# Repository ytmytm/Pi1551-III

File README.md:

# Pi1551-III

A **1551 floppy emulator** for Commodore C16, C116 and Plus/4, in the same mechanical and aesthetic package as the [C64 Pi1541-III](https://github.com/tebl/C64-Pi1541-III): Raspberry Pi 3–based, 1.3" OLED, rotary encoder, and stack of PCBs with faceplates. 

This variant uses the **[Pi1551](https://github.com/ytmytm/Pi1551)** firmware and connects to the computer via **[tcbm2sd](https://github.com/ytmytm/plus4-tcbm2sd)** (TCBM bus). It also adds a **MiniDIN-7** port for **TAP tape playback** with a simple 1:1 male-to-male cable to the machine’s tape port.

> **WARNING — tcbm2sd only**  
> This device must **only** be connected to a **tcbm2sd** adapter. **Do not** connect it to an original 1551 paddle or any other 5 V bus. The interface is **not 5 V tolerant** and can damage the Raspberry Pi and the computer.

---

**Build files:** Gerbers for every board, plus BOM and SMD position files for the main module (Pi1551-III Module-rotated), are published in the **[Releases](https://github.com/ytmytm/Pi1551-III/releases)** section of this repository.

If you prefer a smaller, simpler board: see **[Pi1551-HAT](https://github.com/ytmytm/Pi1551-HAT)** for a minimal Raspberry Pi HAT with the same 1551 + TAP functionality with several features optional.

---

- [1. Modules](#1-modules)
- [2. Differences from Pi1541-III](#2-differences-from-pi1541-iii)
- [3. Assembly](#3-assembly)
- [4. Cables](#4-cables)
- [5. Documentation](#5-documentation)
- [6. Resources](#6-resources)
- [7. Acknowledgements](#7-acknowledgements)

## 1. Modules

A complete Pi1551-III uses the same five-PCB stack as the Pi1541-III. Assembly and mechanical steps are almost identical, so **use the original project’s gallery and docs** for visual guidance:

- **[C64-Pi1541-III gallery](https://github.com/tebl/C64-Pi1541-III/tree/main/gallery)** — build photos, side views, and assembly reference.

(side view of Pi1541-III, almost identical to Pi1551-III)

| Module | Required | Description | Documentation | Build files |
|--------|----------|-------------|---------------|------------|
| [Pi1551-III Module-rotated](Pi1551-III%20Module-rotated) | Yes | Main module: RPi 3, TCBM interface, optional power area (see below), MiniDIN-7 for TAP. | [BOM](Pi1551-III%20Module-rotated/README.md#3-bom) | [Releases](https://github.com/ytmytm/Pi1551-III/releases) |
| [Pi1551-III Module Panel](Pi1551-III%20Module%20Panel) | Yes | Front panel: OLED, rotary encoder, switches. | [BOM](Pi1551-III%20Module%20Panel/README.md#3-bom) | [Releases](https://github.com/ytmytm/Pi1551-III/releases) |
| [Pi1551-III Faceplate (FB1)](faceplates/Pi1551-III%20Module%20FB1) | Yes | Top faceplate; mechanical support for front panel. | — | [Releases](https://github.com/ytmytm/Pi1551-III/releases) |
| [Pi1551-III Faceplate (FB2)](faceplates/Pi1551-III%20Module%20FB2) | Recommended | Bottom faceplate; protects from shorts. | — | [Releases](https://github.com/ytmytm/Pi1551-III/releases) |
| [Pi1551-III Faceplate (FP1)](faceplates/Pi1551-III%20Module%20FP1) | Recommended | Front faceplate; cosmetic. | — | [Releases](https://github.com/ytmytm/Pi1551-III/releases) |

Each module’s BOM is in its README. For the main module, Gerbers, BOM and position files for SMD parts only are also in **Releases** for easy fabrication (e.g. JLCPCB).

## 2. Differences from Pi1541-III

- **Main module (“rotated”)**  
  The Raspberry Pi footprint is **rotated 180°** so **USB and HDMI are accessible** on the outside. I recommend **not** fitting the barrel jack (J1) or the 470 µF capacitor (C6): power the device from the **Raspberry Pi’s USB Micro** port with a good 5 V supply (e.g. 2 A). That avoids the extra power circuitry and is safe and sufficient.

- **1551 / TCBM**  
  The main module is adapted for **1551 emulation** and connects to the computer via a **TCBM bus connector** to a **[tcbm2sd](https://github.com/ytmytm/plus4-tcbm2sd)** adapter. Don't try to connect it to the original 1551 paddle - it will damage RaspberryPi.

- **TAP playback**  
  A **MiniDIN-7** port on the main module connects to the C16/C116/Plus/4 **tape port** with a MiniDIN-7 cable for TAP playback.

- **Branding**  
  Labels use the **Microgramma D Extended Bold** font for a consistent Commodore look.

## 3. Assembly

I had some trouble building the first unit, so here are some hints to make it easier:

1. Start with the [Pi1551-III Module-rotated](Pi1551-III%20Module-rotated):
  - Smallest elements first: SMD (if you solder them by hand), then buzzer, then RPi GPIO connector and TCBM bus connector for the ribbon cable, finally the MiniDIN-7 socket.
  - Since the USB power port is now accessible on the RPi, I recommend not installing the barrel jack or the 470 µF capacitor.
  - The capacitor can make the RPi’s HDMI port hard to use, depending on the plug.

2. Then continue with the [Pi1551-III Module Panel](Pi1551-III%20Module%20Panel):
  - Screw the bottom standoffs for mounting the faceplate **first** — it won’t be possible to turn them once the Module Panel is soldered to the base module.
  -  (bottom left standoff is missing on the photo)
  - Put solder blobs on JP3/JP4 to set up the OLED’s VCC and GND pin order according to your SH1106 module version.
  - 
  - Do a test fit with the buttons (not soldered yet) and the faceplate to confirm their stems are long enough.
  - Solder in the buttons and rotary encoder, then test-fit the faceplate again.
  - Solder the right-angle pin headers to the faceplate. Make sure the two boards are aligned and square. This must happen before OLED screen.
  - Solder in the OLED screen; this is tricky because it must be at just the right distance from the PCB, parallel to it and aligned with the hole in the faceplate. I did the soldering with the faceplate screwed on; a piece of sticky foam behind the OLED to hold it in place can help.
  - 
  - Solder in the rectangular LEDs — as with the OLED, align them with the holes in the faceplate so they sit flush. Their longer legs should be in the holes closer to the outer edge of the board; if you’re unsure about polarity, leave this until the two modules are connected with angled pin headers — with power on you can check which orientation lights the PWR LED.
  - 
  - An authentic 1551 has a green PWR LED and red DRV LED, but their brightness differs a lot; rather than tweaking current-limiting resistors, I recommend using the same colour LED for both indicators.

3. Connect the modules together:
  - Fit the 12-pin right-angle pin headers so the short leg connects to the vertical PCB (Module Panel) and the longer legs go down through the horizontal PCB (Module-rotated).
  - Check that the PCBs are at the correct angle.
  - Ensure the standoffs in the Module Panel’s bottom holes are screwed in.
  - Then solder the first 1–2 pins on each end.
  - Check the angle again before soldering the rest.

At this point the device is basically complete and ready for testing. Remaining mechanical steps (faceplates, etc.) are illustrated in the **[C64-Pi1541-III gallery](https://github.com/tebl/C64-Pi1541-III/tree/main/gallery)** and [assembling one](https://github.com/tebl/C64-Pi1541-III/blob/main/documentation/assembling_one.md). For SD card preparation and firmware configuration, see the **[Pi1551](https://github.com/ytmytm/Pi1551)** project.

## 4. Cables

**TCBM (tcbm2sd):** Use a straight 16-wire ribbon cable; connections are 1:1 and both ends must be crimped the same way. On the Pi1551-III side the cable must be plugged in before the top cover is screwed on. I recommend crimping as in the photo below so the cable runs to the side opposite the plug’s tab, for easier routing.

**Tape (TAP):** You need a 1:1 male-to-male MiniDIN-7 cable. They are available on AliExpress, or you can solder one yourself. When buying a cable, note:
- Both plugs should be straight, not angled.
- The plug may not fit the Plus/4 if the round part of the MiniDIN doesn’t extend far enough from the rectangular body of the plug. Just shave off the corners from the square section. It may not look pretty but it will work. 

If your C16/C116/Plus/4 has a 6510 CPU swap, it cannot drive the tape MOTOR line; you can leave MOTOR enabled all the time in the [Pi1551](https://github.com/ytmytm/Pi1551) config (see [this note](https://hackjunk.com/2017/06/23/commodore-16-plus-4-8501-to-6510-cpu-conversion/)).

## 5. Documentation

SD card setup, configuration options, and firmware behaviour are described in the **[Pi1551](https://github.com/ytmytm/Pi1551)** project on GitHub.

- [Troubleshooting](documentation/troubleshooting.md)

## 6. Resources

- [C64 Pi1541-III](https://github.com/tebl/C64-Pi1541-III) — original design and gallery
- [Pi1551](https://github.com/ytmytm/Pi1551) — 1551 emulator firmware for Raspberry Pi
- [tcbm2sd](https://github.com/ytmytm/plus4-tcbm2sd) — TCBM adapter (connects Pi1551 to C16/C116/Plus/4)
- [Pi1551-HAT](https://github.com/ytmytm/Pi1551-HAT) — compact HAT alternative for 1551 + TAP
- [fat32format](http://ridgecrop.co.uk/index.htm?guiformat.htm) — format SD card as FAT32 (e.g. for Raspberry Pi boot)
- [SD Memory Card Formatter](https://www.sdcard.org/downloads/formatter/) — SD Association tool for formatting SD/SDHC/SDXC cards (Windows/Mac/Linux)

## 7. Acknowledgements

The Pi1551-III mechanical design, panel, and faceplates are derived from **[tebl](https://github.com/tebl)**’s [C64-Pi1541-III](https://github.com/tebl/C64-Pi1541-III), which in turn builds on **Steve White**’s [Pi1541](https://cbm-pi1541.firebaseapp.com/) software.

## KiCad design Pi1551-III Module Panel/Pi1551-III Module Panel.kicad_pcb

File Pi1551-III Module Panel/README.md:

# Pi1551-III Module Panel
This PCB holds the front-panel components and mounts on the [Pi1551-III Module-rotated](../Pi1551-III%20Module-rotated). It has its own BOM; order parts for both this panel and the main module to build a complete device.

- [1> Build instructions](#1-build-instructions)
- [2> Schematic](#2-schematic)
- [3> BOM](#3-bom)

# 1> Build instructions
Assembly of this panel is described in the top-level [README Assembly section](../README.md#3-assembly) (step 2). The BOM for this module is [below](#3-bom). For more photos and the same mechanical steps, see the [C64-Pi1541-III gallery](https://github.com/tebl/C64-Pi1541-III/tree/main/gallery).

# 2> Schematic
The supplied KiCad files should be sufficient as both a schematic and as a  starting point for ordering PCBs (basically you could just zip the contents of the export folder and upload that on a fabrication site), the schematic is also available in [PDF-format](../documentation/schematic) (if present in this repo) for when things don’t work as expected after assembly.

# 3> BOM
This BOM matches the schematic in this folder. Optional parts in parentheses. Build files (Gerbers, etc.) are in the [Releases](https://github.com/ytmytm/Pi1551-III/releases) section.

| Reference             | Item                                                              | Count | Order  |
| --------------------- | ----------------------------------------------------------------- | ----- | ------ |
| Module Panel PCB      | PCB specific to this project                                      |     1 | [Releases](https://github.com/ytmytm/Pi1551-III/releases)
| Faceplate (FP1) PCB   | Front faceplate                                                   |    (1)| [Releases](https://github.com/ytmytm/Pi1551-III/releases)
| IC1 *1                | SH1106 I2C OLED 128x64 (1.3")                                     |     1 |
| ENC1                  | EC11 rotary encoder, 20mm. Preferably plum handle.                |     1 |
|                       | Suitable knob for rotary encoder, max 20mm in diameter.           |    (1)|
| D1,D2                 | 2x5x7mm rectangular LED, suitably coloured.                       |     2 |
| J1                    | 12-pin right-angle pin header                                     |     1 |
| SW1,SW2               | 6x6mm momentary switch, 10.5mm or taller.                         |     2 |
| Mounting *2           | Nylon M3 hex standoffs 8mm (M-F)                                  |     4 |
| Mounting *2           | Nylon M3x6mm nylon screws                                         |     4 |
| Mounting *2           | Nylon M3x6mm nylon nuts                                           |     4 |

1) Many of these will be listed for sale as 1.3" ssd1306-based OLED displays, but they actually have the slightly different sh1106-controller. Something to keep in mind when ordering.
2) These are used in various places of the project, these are available in the form of kits usually advertised *M3 nylon standoff kit* which should contain most of what you'd need though you should check that they include them in sufficient quantity.

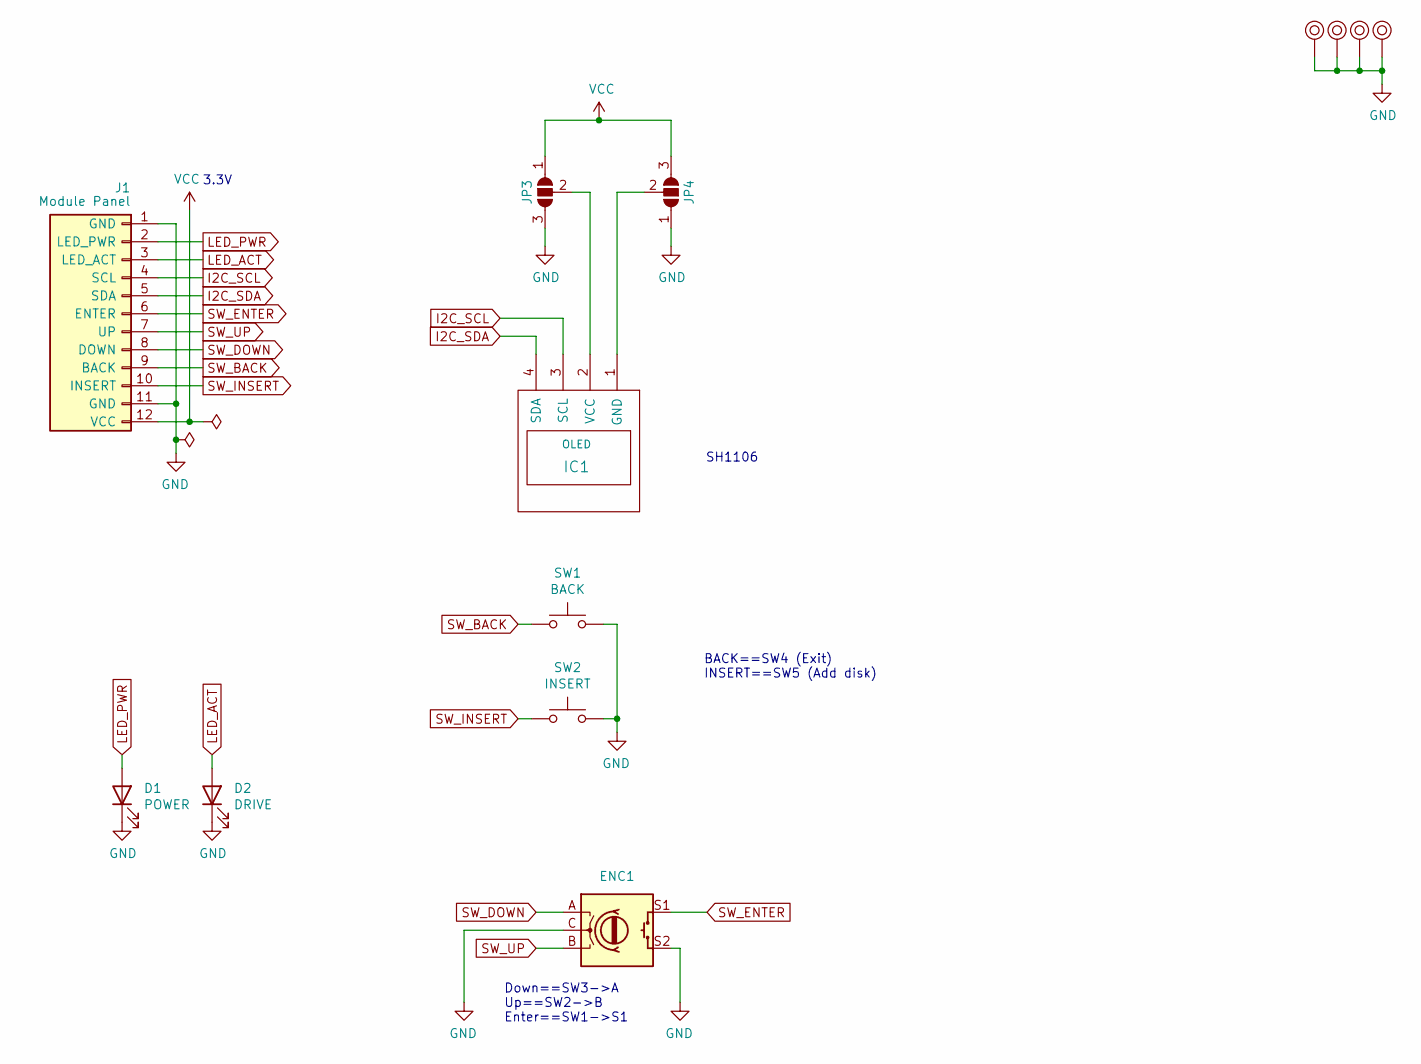
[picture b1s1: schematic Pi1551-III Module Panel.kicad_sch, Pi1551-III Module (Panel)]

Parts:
D1: POWER; LED_Rectangular_W3.0mm_H2.0mm
D2: DRIVE; LED_Rectangular_W3.0mm_H2.0mm
ENC1: RotaryEncoder_Switch; RotaryEncoder_Alps_EC11E-Switch_Vertical_H20mm_CircularMoun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; MFR.Part # EC11E15244B2; JLCPCB Part # C470754
IC1: OLED; 1.3_I2C_OLED_No_mounting
J1: Module Panel; PinHeader_1x12_P2.54mm_Horizontal
JP3, JP4: SolderJumper_3_Open; SolderJumper-3_P1.3mm_Open_RoundedPad1.0x1.5mm_NumberLabels
M1, M2, M3, M4: Mounting_Pin; M3_pin
SW1: BACK; SW_PUSH_6mm
SW2: INSERT; SW_PUSH_6mm

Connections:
GND: D1.1 (K), D2.1 (K), ENC1.C, ENC1.S2, J1.1 (GND), J1.11 (GND), JP3.3 (B), JP4.1 (A), M1.1, M2.1, M3.1, M4.1, SW1.2, SW2.2
I2C_SCL: IC1.3 (SCL), J1.4 (SCL)
I2C_SDA: IC1.4 (SDA), J1.5 (SDA)
LED_ACT: D2.2 (A), J1.3 (LED_ACT)
LED_PWR: D1.2 (A), J1.2 (LED_PWR)
unnamed: IC1.1 (GND), JP4.2 (C)
unnamed: IC1.2 (VCC), JP3.2 (C)
SW_BACK: J1.9 (BACK), SW1.1
SW_DOWN: ENC1.A, J1.8 (DOWN)
SW_ENTER: ENC1.S1, J1.6 (ENTER)
SW_INSERT: J1.10 (INSERT), SW2.1
SW_UP: ENC1.B, J1.7 (UP)
VCC: J1.12 (VCC), JP3.1 (A), JP4.3 (B)

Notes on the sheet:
BACK==SW4 (Exit) INSERT==SW5 (Add disk)
SH1106
Down==SW3->A Up==SW2->B Enter==SW1->S1
3.3V

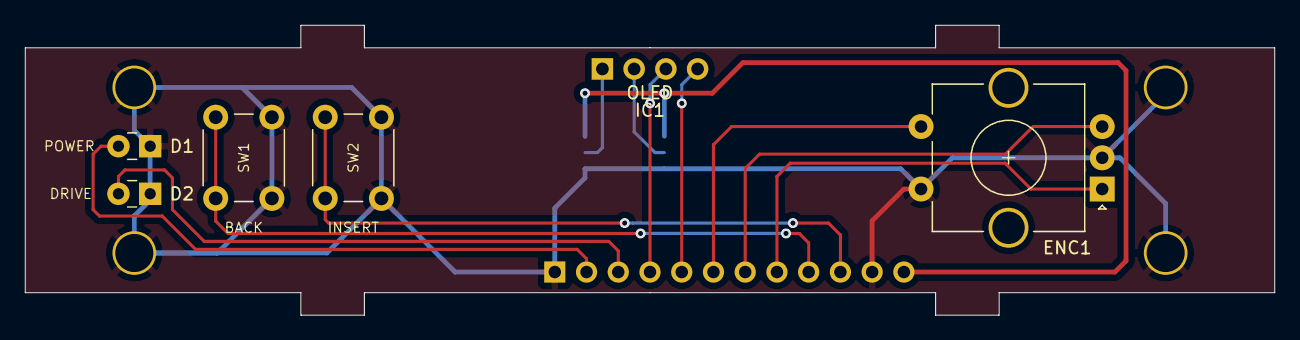
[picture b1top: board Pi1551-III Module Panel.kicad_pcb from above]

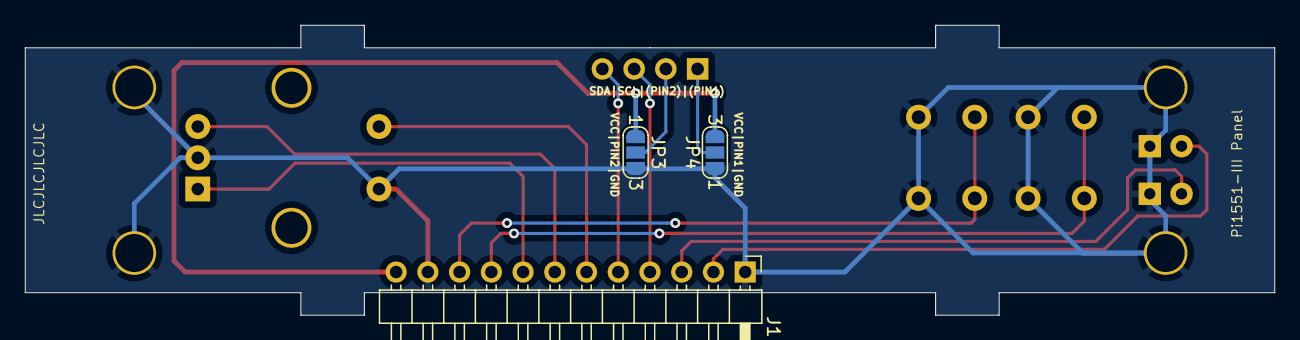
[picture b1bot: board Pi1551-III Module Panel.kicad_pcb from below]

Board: 2 copper layers, 100.0 x 23.2 mm, 13 parts (3 on the bottom side), 13 nets.

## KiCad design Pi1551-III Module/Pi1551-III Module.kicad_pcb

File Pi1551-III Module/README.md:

# Pi1551-III Module
This is the main PCB and will hold most of the active components in the device, but note that it is designed to be used with [Pi1551-III Module Panel](https://github.com/tebl/Pi1551-III/tree/main/Pi1551-III%20Module%20Panel) and has one listed in the [BOM](#3-bom). Note that the mentioned panel also has its own separate [BOM](https://github.com/tebl/Pi1551-III/tree/main/Pi1551-III%20Module%20Panel/README.md#3-bom), so keep that in mind while ordering components.

- [1> Build instructions](#1-build-instructions)
- [2> Schematic](#2-schematic)
- [3> BOM](#3-bom)

# 1> Build instructions
Assembling this module is covered as part of the overall documentation, as linked below. Note that *BOM* is supplied per module, the one belonging to this module in particular is included as part of this document (click [here](#3-bom) to go there).

- [Assembling one](https://github.com/tebl/Pi1551-III/blob/main/documentation/assembling_one.md)

# 2> Schematic
The supplied KiCad files should be sufficient as both a schematic and as a  starting point for ordering PCBs (basically you could just zip the contents of the export folder and upload that on a fabrication site), the schematic is also available in [PDF-format](https://github.com/tebl/Pi1551-III/tree/main/documentation/schematic) and this is what you'll need to print and work your way through this things don't work as expected after assembly.

# 3> BOM
Most parts should be easy to get a hold of from your favourite local electronic component shop, but given that I don't have access to such shops where I live so everything was based on whatever I could get cheapest from eBay/AliExpress (free shipping, but plan on waiting 3-4 weeks for delivery). Components in parenthesis can be considered optional for features beyond the more basic functionality, but where's the fun in that? You deserve the complete package.

| Reference             | Item                                                              | Count | Order  |
| --------------------- | ----------------------------------------------------------------- | ----- | ------ |
| Module PCB            | PCB specific to this project                                      |     1 | [See modules](https://github.com/tebl/Pi1551-III/blob/main/README.md#1-modules)
| Faceplate (FB1) PCB   | Top faceplate                                                     |     1 | [See modules](https://github.com/tebl/Pi1551-III/blob/main/README.md#1-modules)
| Faceplate (FB2) PCB   | Bottom faceplate                                                  |    (1)| [See modules](https://github.com/tebl/Pi1551-III/blob/main/README.md#1-modules)
| A1                    | 2x20 pin female header                                            |     1 |
|                       | Raspberry Pi version 3B,3B+ or 3A+                                |     1 |
| A2 *1                 | 4ch I2C level converter module                                    |     1 |
| BZ1                   | Passive buzzer (pin spacing from 3.81 to 7mm will work)           |   (1) |
| C1                    | 100nF ceramic capacitor (5mm)                                     |     1 |
| C6                    | 470uF electrolytic capacitor (8mm x 3.5mm)                        |     1 |
| J1                    | 2.1mm x 5.5mm barrel plug                                         |     1 |
| J2,J3                 | Female S-terminal 6-pin DIN PCB                                   |  1 (1)|
| J8                    | [Pi1551-III Module Panel](https://github.com/tebl/Pi1551-III/tree/main/Pi1551-III%20Module%20Panel) (completed unit) | 1 |
| R1,R2                 | 1k Ohm resistor                                                   |     2 |
| R3,R4                 | 10k Ohm resistor                                                  |     2 |
| R6,R7 *2              | 470 Ohm resistor                                                  |     2 |
| U1 *3                 | 7406 (DIP-14)                                                     |     1 |
| Mounting *4           | Nylon M3 hex standoffs 6mm (M-F)                                  |     4 |
| Mounting *4           | Nylon M3 hex standoffs 8mm (M-F)                                  |     2 |
| Mounting *5           | Nylon M3 hex standoffs 12mm (M-F)                                 |    (4)|
| Mounting *4           | Nylon M3 hex standoffs 20mm (M-F)                                 |     4 |
| Mounting *4           | Nylon M3x6mm nylon screws                                         |     6 |
| Mounting *4           | Nylon M3x6mm nylon nuts                                           |     12 |

1) There are multiple configurations of these being sold, this is usually sold with a blue PCB. When in doubt, compare the sale listing with the one shown in this [image](https://raw.githubusercontent.com/tebl/Pi1551-III/main/gallery/build_006B.jpg).
2) This is the resistor for the LEDs mounted on [Pi1551-III Module Panel](https://github.com/tebl/Pi1551-III/tree/main/Pi1551-III%20Module%20Panel), the value need to be sized according to the type of LED being used. This value is a somewhat safe choice cheaper coloured LEDs, for anything blue or especially marked as being *bright* - then you need to calculate a proper value for these.
3) There are unfortunately counterfeit 7406-chips being circulated, the ones I've had the most success with has been marked 7406PC though a handful of SN7406 have also been found working. See [troubleshooting](https://github.com/tebl/Pi1551-III/blob/main/documentation/troubleshooting.md) for more information.
4) These are used in various places of the project, these are available in the form of kits usually advertised *M3 nylon standoff kit* which should contain most of what you'd need though you should check that they include them in sufficient quantity.
5) These are only needed when *NOT* installing bottom faceplate ([Pi1551-III Faceplate (FB2)](https://github.com/tebl/Pi1551-III/tree/main/faceplates/Pi1551-III%20Module%20FB2))

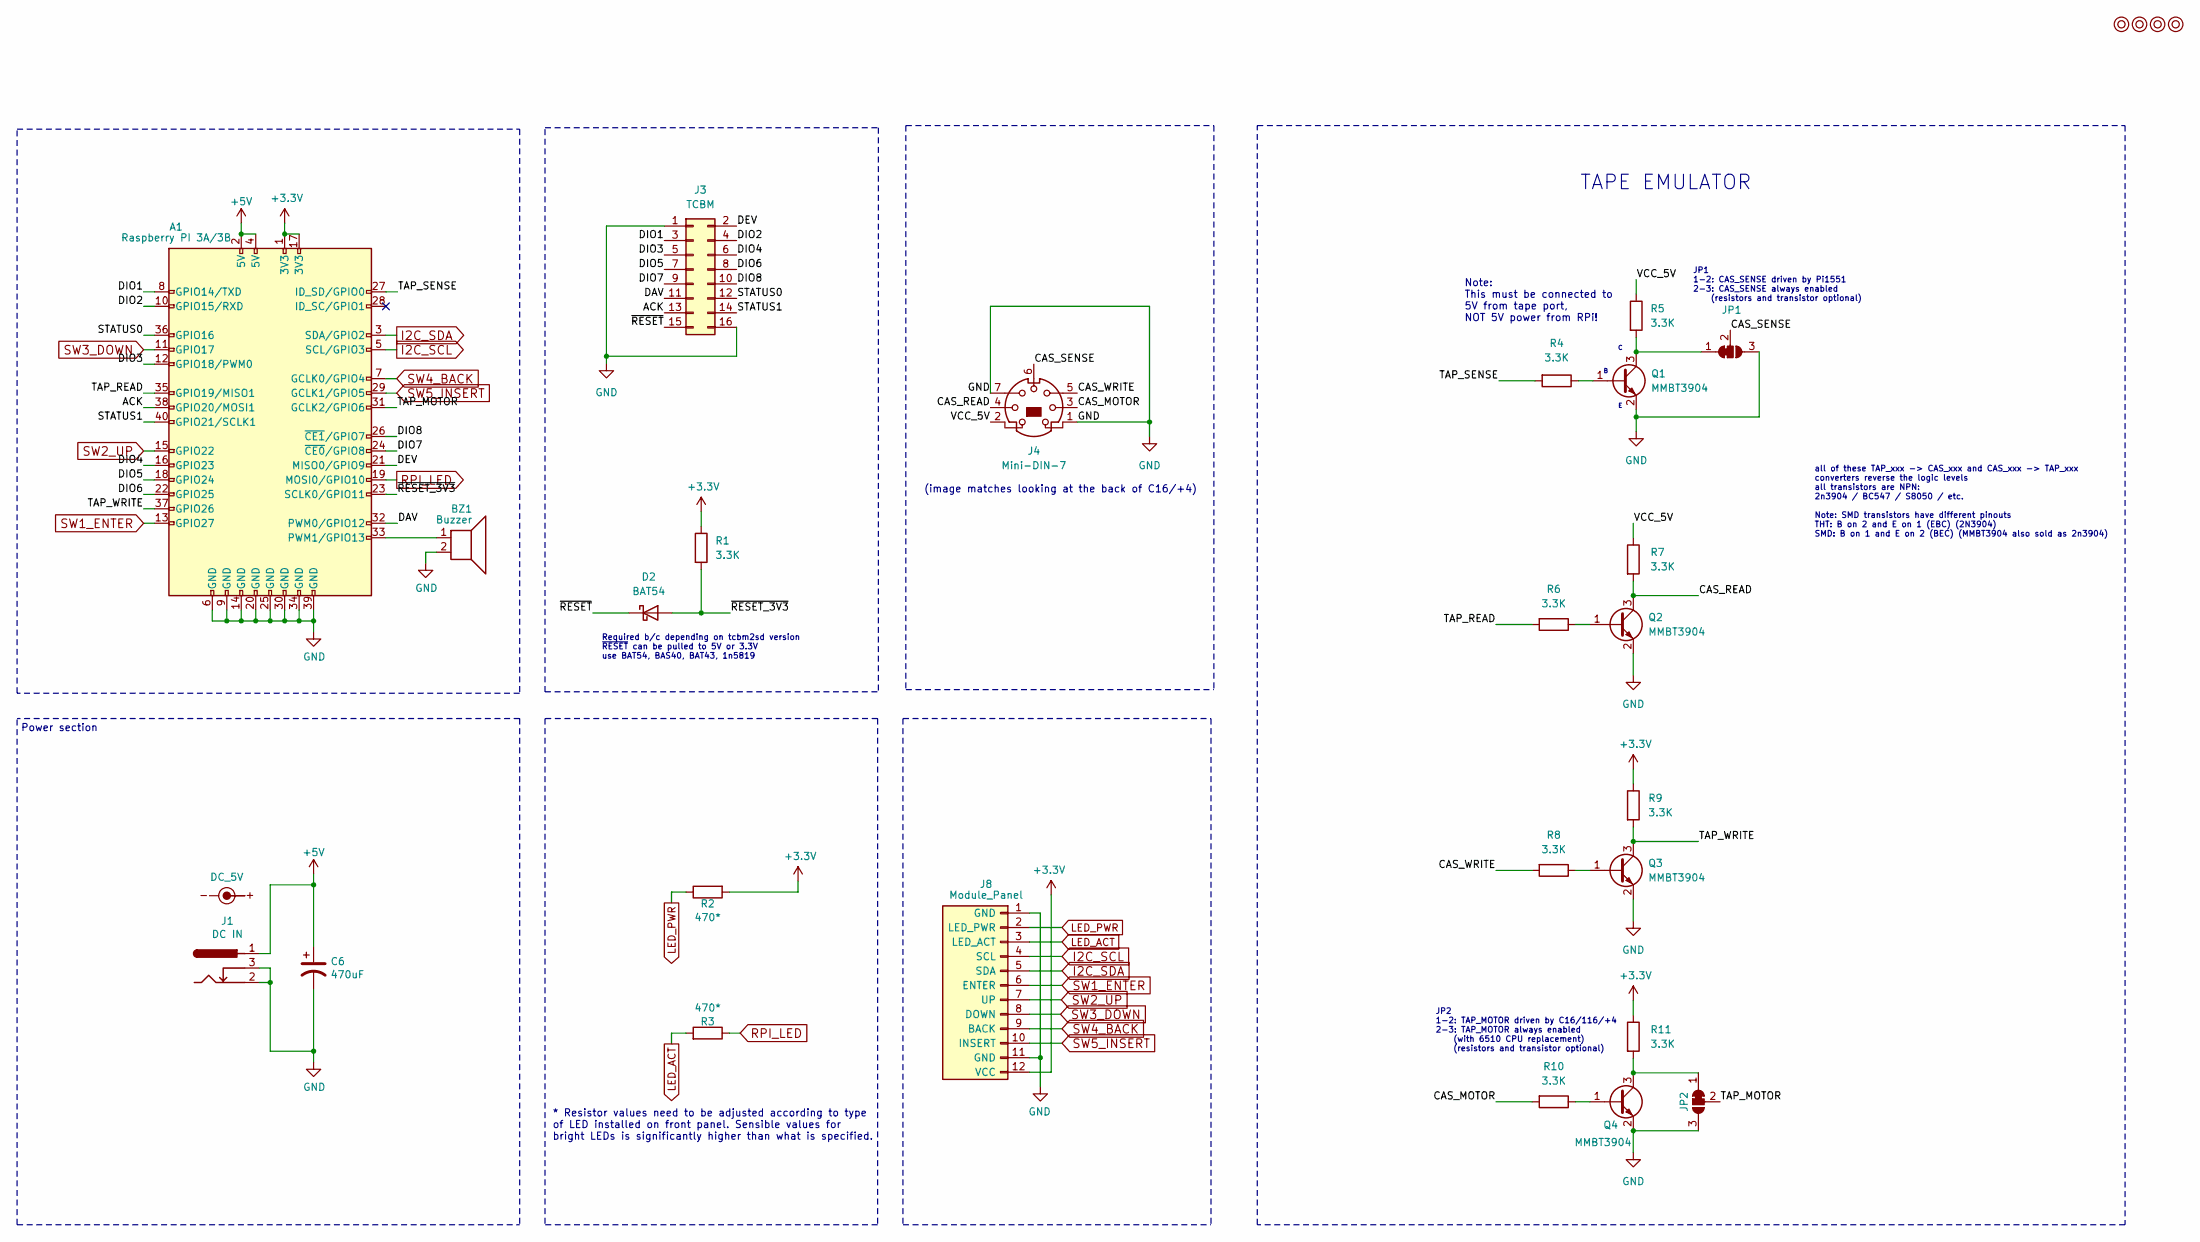
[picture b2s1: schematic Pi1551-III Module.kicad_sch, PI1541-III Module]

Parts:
A1: Raspberry PI 3A/3B; Raspberry_Pi_3B_Socketed_THT_FaceDown_MountingHoles
BZ1: Buzzer; Buzzer_12x9.5RM7.6
C6: 470uF; CP_Radial_D8.0mm_P3.50mm
D2: BAT54; D_SOD-123; MFR.Part # BAT54W; JLCPCB Part # C7502705
J1: DC IN; BARREL_JACK
J3: TCBM; IDC-Header_2x08_P2.54mm_Vertical
J4: Mini-DIN-7; Mini_DIN_round_7_canned
J8: Module_Panel
JP1, JP2: SolderJumper_3_Bridged12; SolderJumper-3_P1.3mm_Bridged12_RoundedPad1.0x1.5mm_NumberL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
M1, M2, M3, M4: Mounting; M3
Q1, Q2, Q3, Q4: MMBT3904; SOT-23_Handsoldering; MFR.Part # 2N3904S-RTK/PS; JLCPCB Part # C18536
R1, R4, R5, R6, R7, R8, R9, R10, R11: 3.3K; R_0805_2012Metric_Pad1.20x1.40mm_HandSolder; MFR.Part # 0805W8F3301T5E; JLCPCB Part # C26010
R2, R3: 470*; R_0805_2012Metric_Pad1.20x1.40mm_HandSolder; MFR.Part # 0805W8F4700T5E; JLCPCB Part # C17710
SYM1: DC_5V; PWR_Specification

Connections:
+3.3V: A1.1 (3V3), A1.17 (3V3), J8.12 (VCC), R1.1, R2.2, R9.1, R11.1
+5V: A1.2 (5V), A1.4 (5V), C6.1, J1.1
/ACK: A1.38 (GPIO20/MOSI1), J3.13
/CAS_MOTOR: J4.3, R10.2
/CAS_READ: J4.4, Q2.3 (C), R7.2
/CAS_SENSE: J4.6, JP1.2 (C)
/CAS_WRITE: J4.5, R8.2
/DAV: A1.32 (PWM0/GPIO12), J3.11
/DEV: A1.21 (MISO0/GPIO9), J3.2
/DIO1: A1.8 (GPIO14/TXD), J3.3
/DIO2: A1.10 (GPIO15/RXD), J3.4
/DIO3: A1.12 (GPIO18/PWM0), J3.5
/DIO4: A1.16 (GPIO23), J3.6
/DIO5: A1.18 (GPIO24), J3.7
/DIO6: A1.22 (GPIO25), J3.8
/DIO7: A1.24 (~CE0/GPIO8), J3.9
/DIO8: A1.26 (~CE1/GPIO7), J3.10
/STATUS0: A1.36 (GPIO16), J3.12
/STATUS1: A1.40 (GPIO21/SCLK1), J3.14
/TAP_MOTOR: A1.31 (GCLK2/GPIO6), JP2.2 (C)
/TAP_READ: A1.35 (GPIO19/MISO1), R6.2
/TAP_SENSE: A1.27 (ID_SD/GPIO0), R4.2
/TAP_WRITE: A1.37 (GPIO26), Q3.3 (C), R9.2
/VCC_5V: J4.2, R5.1, R7.1
/~RESET_3V3: A1.23 (SCLK0/GPIO11), D2.2 (A), R1.2
/~RESET: D2.1 (K), J3.15
GND: A1.6 (GND), A1.9 (GND), A1.14 (GND), A1.20 (GND), A1.25 (GND), A1.30 (GND), A1.34 (GND), A1.39 (GND), BZ1.2, C6.2, J1.2, J1.3, J3.1, J3.16, J4.1, J4.7, J8.1 (GND), J8.11 (GND), JP1.3 (B), JP2.3 (B), Q1.2 (E), Q2.2 (E), Q3.2 (E), Q4.2 (E)
I2C_SCL: A1.5 (SCL/GPIO3), J8.4 (SCL)
I2C_SDA: A1.3 (SDA/GPIO2), J8.5 (SDA)
LED_ACT: J8.3 (LED_ACT), R3.2
LED_PWR: J8.2 (LED_PWR), R2.1
unnamed: A1.33 (PWM1/GPIO13), BZ1.1
unnamed: JP1.1 (A), Q1.3 (C), R5.2
unnamed: JP2.1 (A), Q4.3 (C), R11.2
unnamed: Q1.1 (B), R4.1
unnamed: Q2.1 (B), R6.1
unnamed: Q3.1 (B), R8.1
unnamed: Q4.1 (B), R10.1
RPI_LED: A1.19 (MOSI0/GPIO10), R3.1
SW1_ENTER: A1.13 (GPIO27), J8.6 (ENTER)
SW2_UP: A1.15 (GPIO22), J8.7 (UP)
SW3_DOWN: A1.11 (GPIO17), J8.8 (DOWN)
SW4_BACK: A1.7 (GCLK0/GPIO4), J8.9 (BACK)
SW5_INSERT: A1.29 (GCLK1/GPIO5), J8.10 (INSERT)

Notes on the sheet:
(image matches looking at the back of C16/+4)
Required b/c depending on tcbm2sd version ~{RESET} can be pulled to 5V or 3.3V use BAT54, BAS40, BAT43, 1n5819
* Resistor values need to be adjusted according to type of LED installed on front panel. Sensible values for bright LEDs is significantly higher than what is specified.
all of these TAP_xxx -> CAS_xxx and CAS_xxx -> TAP_xxx converters reverse the logic levels all transistors are NPN: 2n3904 / BC547 / S8050 / etc. Note: SMD transistors have different pinouts THT: B on 2 and E on 1 (EBC) (2N3904) SMD: B on 1 and E on 2 (BEC) (MMBT3904 also sold as 2n3904)
Note: This must be connected to 5V from tape port, NOT 5V power from RPi!
TAPE EMULATOR
Power section
JP2 1-2: TAP_MOTOR driven by C16/116/+4 2-3: TAP_MOTOR always enabled (with 6510 CPU replacement) (resistors and transistor optional)
JP1 1-2: CAS_SENSE driven by Pi1551 2-3: CAS_SENSE always enabled (resistors and transistor optional)

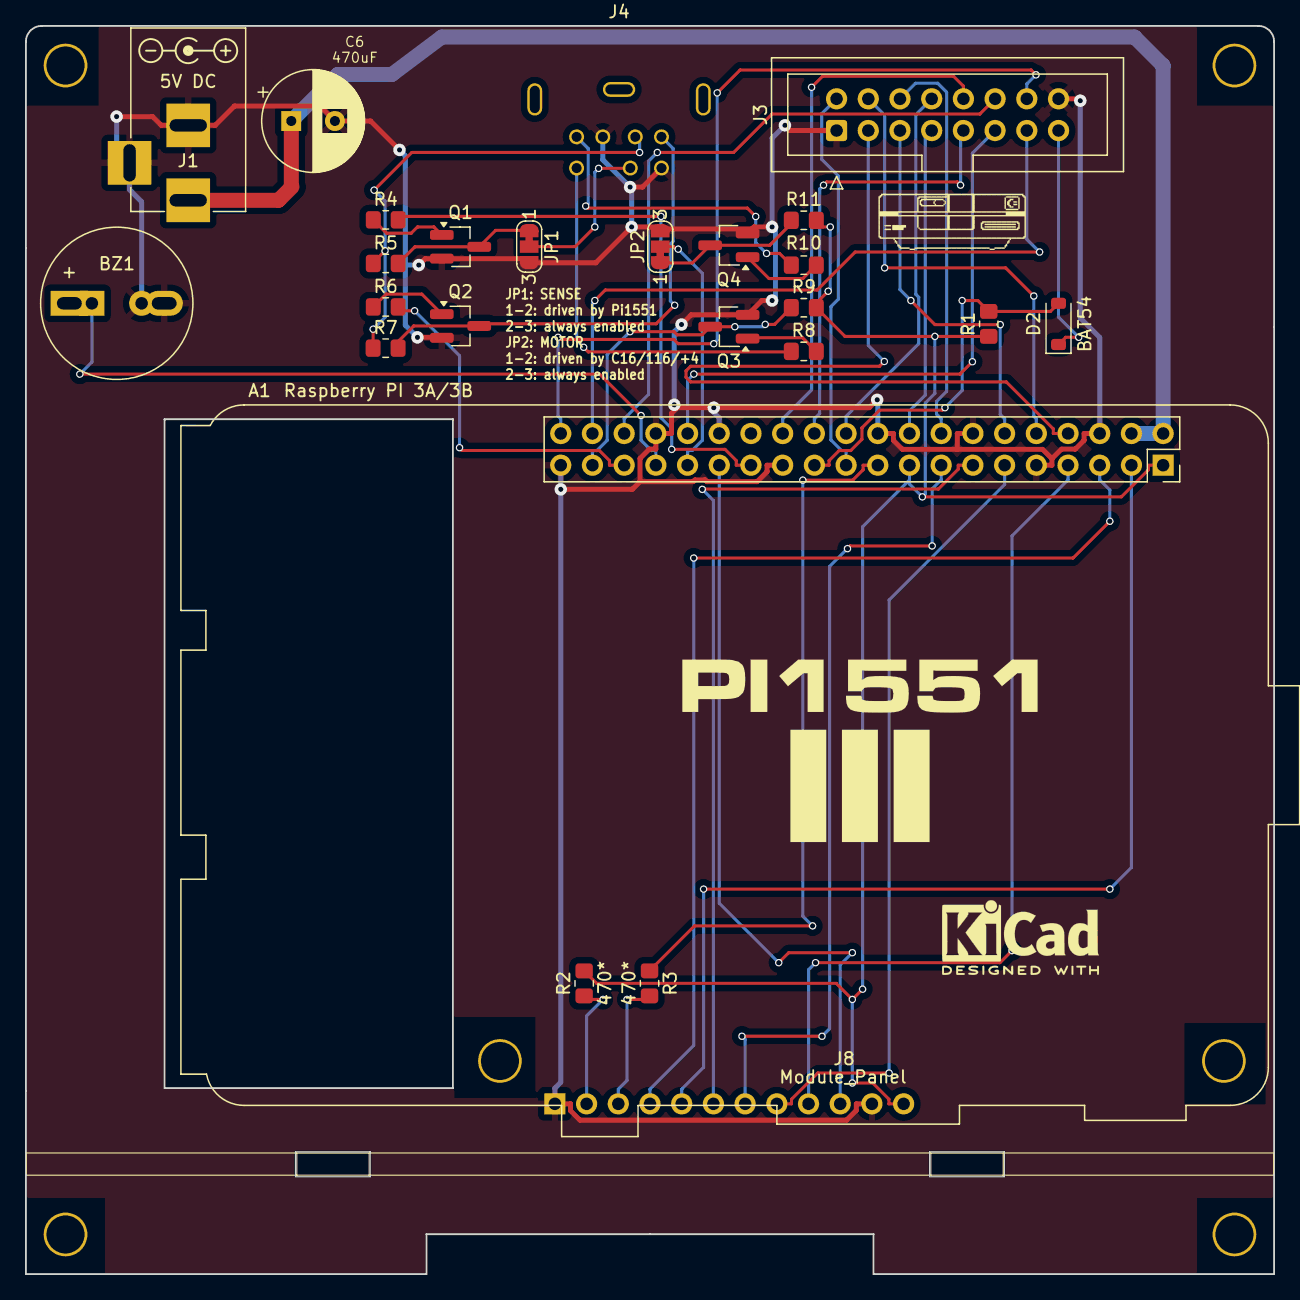
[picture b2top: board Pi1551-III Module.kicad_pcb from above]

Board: 2 copper layers, 100.0 x 100.0 mm, 35 parts (1 on the bottom side), 44 nets.

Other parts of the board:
Pi1541-drive: Pi1541-drive
REF1, REF2: KiCad-Logo2_6mm_SilkScreen
kibuzzard-69864AC5: G***; kibuzzard-69864AC5
kibuzzard-69864AE8: G***; kibuzzard-69864AE8

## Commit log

2026-02-02 rebranding to Pi1551-III
2026-02-02 upgrade to KiCad 9.0.7
2026-02-02 ignore footprint cache
2026-02-02 cleanups
2026-02-06 PI1551 branding and Microgramma font labels
2026-02-06 MiniDin connectors from https://forum.kicad.info/t/mini-din-connectors-their-footprints-and-3-d-models-asking-for-discuss
2026-02-07 rotated RPi version to get access to all the ports
2026-02-07 all 10K resistors to 3.3K, JLPCB part numbers for 470R resistors, 1.2mm track width for 5V - as short as possible
2026-02-09 gerber files for fabrication
2026-03-03 change jumpers to be open - it's too difficult to cut them once panel is soldered in
2026-03-03 remove base module PCB with RPi in original orientation, no need to keep it
2026-03-03 PI1551-III in action
2026-03-04 updated documentation
2026-03-04 remove Pi1541-III gallery
2026-03-04 updated docs
2026-03-04 ignore some files
2026-03-04 no need for duplicated schematic
2026-03-04 correct path
2026-03-08 Tape cable hint
2026-03-10 revision 2 - pullups on all TCBM lines
2026-03-10 updated BOM with pullups
    Updated resistor count and description for R4–R24.
